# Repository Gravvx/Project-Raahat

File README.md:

# 🚁 Project RAAHAT
> **Rapid Aerial AI for Hazard Assessment & Tracking**  
> *Developed by Team Sutra for the Smart India Hackathon*

Project RAAHAT is an Edge-AI powered autonomous UAV reconnaissance system designed for rapid disaster search-and-rescue (SAR) operations. 

Built for the Smart India Hackathon, the platform utilizes a **Software-in-the-Loop (SITL)** architecture to simulate drone flight physics, perform entirely offline on-device AI inference, and mathematically map 2D video pixel detections into precise 3D real-world GPS coordinates for emergency responders — backed by a validated custom hardware payload designed for real-world deployment.

---

## 📑 Table of Contents
- [System Architecture](#-system-architecture)
- [Hardware Architecture](#-hardware-architecture)
- [Directory Structure](#-directory-structure)
- [Mathematical Core: Pixel-to-GPS](#-mathematical-core-pixel-to-gps)
- [Installation & Prerequisites](#-installation--prerequisites)
- [Operational Guide (Usage)](#-operational-guide-usage)
- [Dashboard Features (ARES-C2)](#-dashboard-features-ares-c2)

---

## 🏗️ System Architecture

To ensure safety, rapid iteration, and hardware-readiness, Project RAAHAT is built on **4 foundational pillars**:

1. **SITL Simulation (Webots):** Simulates a DJI Mavic 2 Pro with physically accurate IMU, GPS, and optical sensors. The Python-based controller acts as the flight computer, running Boustrophedon (lawnmower) autonomous search patterns via PID stabilization.
2. **Edge-AI Computer Vision:** Utilizes YOLOv8n optimized for edge GPUs alongside ByteTrack. This ensures real-time victim detection while preventing duplicate counting of the same survivor across consecutive video frames.
3. **Hardware Payload & Power System:** A custom-designed carrier PCB integrating the compute, sensing, and communication stack onto the physical airframe.
4. **ARES-C2 Ground Control Station:** A monolithic, Python-native Streamlit dashboard styled to MIL-STD-1472H defense ergonomics. It provides responders with live telemetry, offline map rendering, and geo-triage audit logs.

---

## 🔧 Hardware Architecture

Project RAAHAT's hardware stack is engineered so all AI inference happens onboard, ensuring functionality even when network connectivity is entirely unavailable at a disaster site.

### Compute & Sensing

| Component | Role |
| :--- | :--- |
| **NVIDIA Jetson Orin Nano** | Edge AI compute — runs YOLOv8n inference locally (CUDA-accelerated) |
| **RGB Camera** | Visual-spectrum survivor and hazard detection |
| **Thermal Camera (LWIR)** | Heat-signature detection for survivors under debris / low-visibility conditions |
| **Pixhawk / STM32** | Real-time flight stabilization, independent of the AI compute layer |
| **NEO-M8N GPS Module** | Positioning data for geo-tagging detections |
| **IMU + Barometer** | Orientation and altitude sensing, feeds flight controller |
| **SX1276 LoRa Transceiver** | Long-range, low-bandwidth telemetry link to ground station (868 MHz) |

### Power System

| Component | Spec |
| :--- | :--- |
| **Main Battery** | 4S / 6S LiPo |
| **Buck Converter (Compute Rail)** | 19V / 5A → Jetson Orin Nano |
| **Buck Converter (Avionics Rail)** | 5V / 4A → Flight controller, IMU, GPS |
| **Power Distribution Board (PDB)** | Routes raw battery voltage to ESCs/motors and both converted rails |

### Custom Carrier PCB & Physical Integration
* **KiCad Verification:** Fully designed project schematic verified with zero Electrical Rules Check (ERC) errors.
* **RF Optimization:** Includes a Pi-filter LC matching network for optimal LoRa RF output on 868 MHz.
* **Physical Assembly:** Sourced accurate `.STEP` CAD files for the airframe, Jetson Orin Nano, and FPV camera module to verify 30.5 × 30.5 mm standoff mounting feasibility and dual payload bay clearance.

### Data Flow (Hardware → Software Bridge)

```text
[RGB + Thermal Cameras] ──▶ Jetson Orin Nano (YOLOv8 Inference)
                                      │
[Pixhawk GPS/IMU] ─────────▶ MAVLink  │
                             Telemetry│
                                      ▼
                        [Compact JSON Alert] 
                                      │
                                    (UART)
                                      │
                                      ▼
                          [LoRa Transmitter (SX1276)]
                                      │
                                (868 MHz RF)
                                      │
                                      ▼
                          [Ground Base Station]
                                      │
                                      ▼
                             [ARES-C2 Dashboard]

SIH_DRONE_PROJECT/
├── webots/                     # SITL Simulation Environment
│   ├── controllers/
│   │   └── autonomous_patrol/
│   │       ├── autonomous_patrol.py  # Drone Flight Controller & PID Logic
│   │       ├── telemetry.json        # Live data bridge to GCS
│   │       └── yolov8n.pt            # Edge AI Model weights
│   ├── mavic2pro/              # UAV Physical Models & Protocols
│   └── worlds/                 # Simulated Disaster Environments
├── hardware/                   # Physical Hardware Design Assets
│   ├── pcb/
│   │   ├── DRONE_SIH.kicad_sch  # Schematic
│   │   └── DRONE_SIH.kicad_pcb  # Board layout (Edge.Cuts verified)
│   ├── cad/
│   │   ├── airframe.step             # Drone airframe STEP file
│   │   ├── jetson_orin_nano.step     # Compute module STEP file
│   │   └── fpv_camera.step           # Camera module STEP file
│   └── renders/                      # KiCad 3D raytraced board renders
├── dashboard.py                # ARES-C2 Tactical Ground Control UI
├── test_ai.py                  # Standalone YOLO inference testing script
└── yolov8n.pt                  # Root AI weights for local dashboard video testing

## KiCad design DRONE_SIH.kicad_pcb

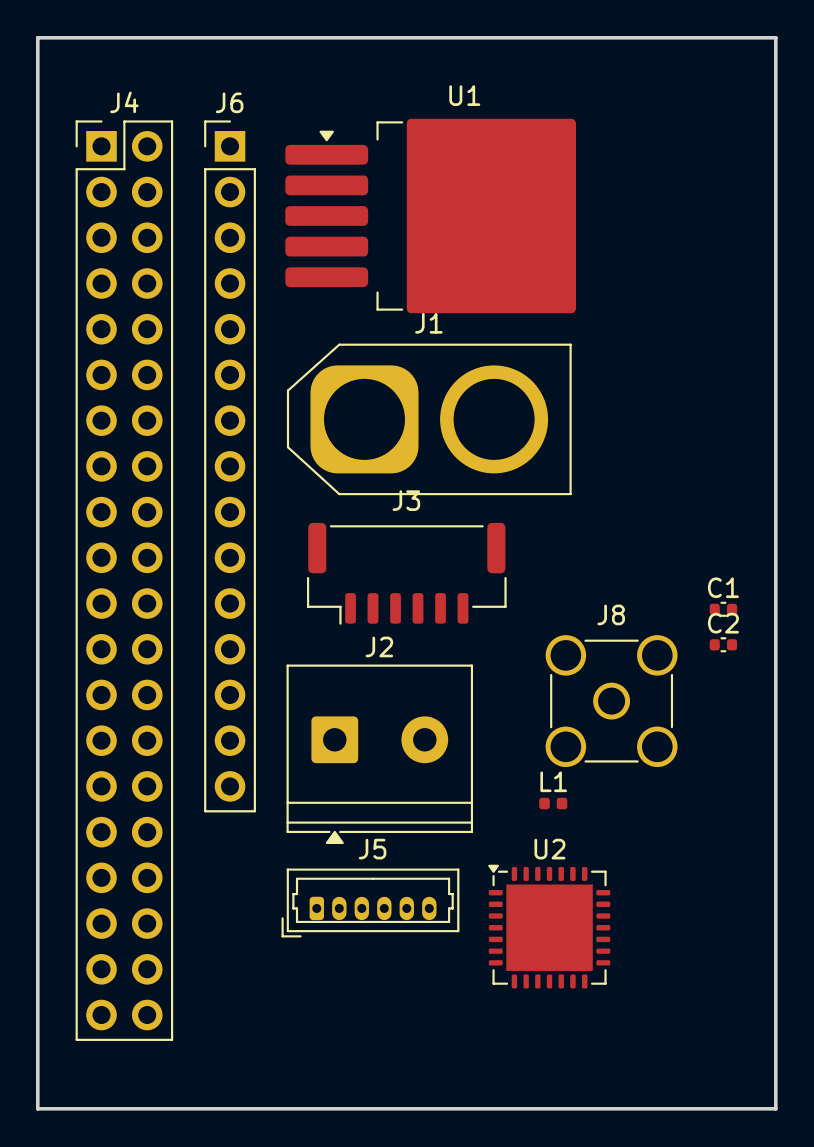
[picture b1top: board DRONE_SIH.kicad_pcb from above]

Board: 2 copper layers, 41.0 x 59.5 mm, 12 parts (0 on the bottom side), 13 nets, no tracks yet.

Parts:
C1: 3.3pF; C_0402_1005Metric
C2: 3.3pH; C_0402_1005Metric
J1: XT60-M; AMASS_XT60-M_1x02_P7.20mm_Vertical
J2: Conn_01x02; TerminalBlock_Phoenix_PT-1,5-2-5.0-H_1x02_P5.00mm_Horizontal
J3: Conn_01x06_Pin; JST_GH_BM06B-GHS-TBT_1x06-1MP_P1.25mm_Vertical
J4: Raspberry_Pi_2_3; PinHeader_2x20_P2.54mm_Vertical
J5: Conn_01x06_Pin; Molex_PicoBlade_53047-0610_1x06_P1.25mm_Vertical
J6: Conn_01x15_Pin; PinHeader_1x15_P2.54mm_Vertical
J8: Conn_Coaxial; SMA_Amphenol_132134-11_Vertical
L1: 4.7nH; L_0402_1005Metric
U1: LM2596S-5; TO-263-5_TabPin3
U2: SX1276; QFN-28-1EP_6x6mm_P0.65mm_EP4.8x4.8mm

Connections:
unnamed: C1.2, C2.2, L1.1
unnamed: J2.2, J4.6 (GND), J4.9 (GND), J4.14 (GND), J4.20 (GND), J4.25 (GND), J4.30 (GND), J4.34 (GND), J4.39 (GND), L1.2, U1.3 (GND), U1.5 (~ON/OFF), U2.15 (GND), U2.23 (GND), U2.26 (GND), U2.29 (GND)
unnamed: U1.2 (OUT), U1.4 (FB)
unnamed: J4.22 (GPIO25), U2.8 (DIO0)
unnamed: J4.21 (MISO0/GPIO9), U2.17 (MISO)
unnamed: J4.19 (MOSI0/GPIO10), U2.18 (MOSI)
unnamed: J4.23 (SCLK0/GPIO11), U2.16 (SCK)
unnamed: J4.24 (~CE0/GPIO8), U2.19 (NSS)
unnamed: J4.1 (3V3), J4.17 (3V3)
unnamed: C2.1, J8.2 (Ext)
unnamed: J8.1 (In), U2.27 (PA_BOOST)
unnamed: C1.1, U2.1 (RFI_LF)
unnamed: J4.2 (5V), J4.4 (5V), U2.3 (VBAT_ANA)

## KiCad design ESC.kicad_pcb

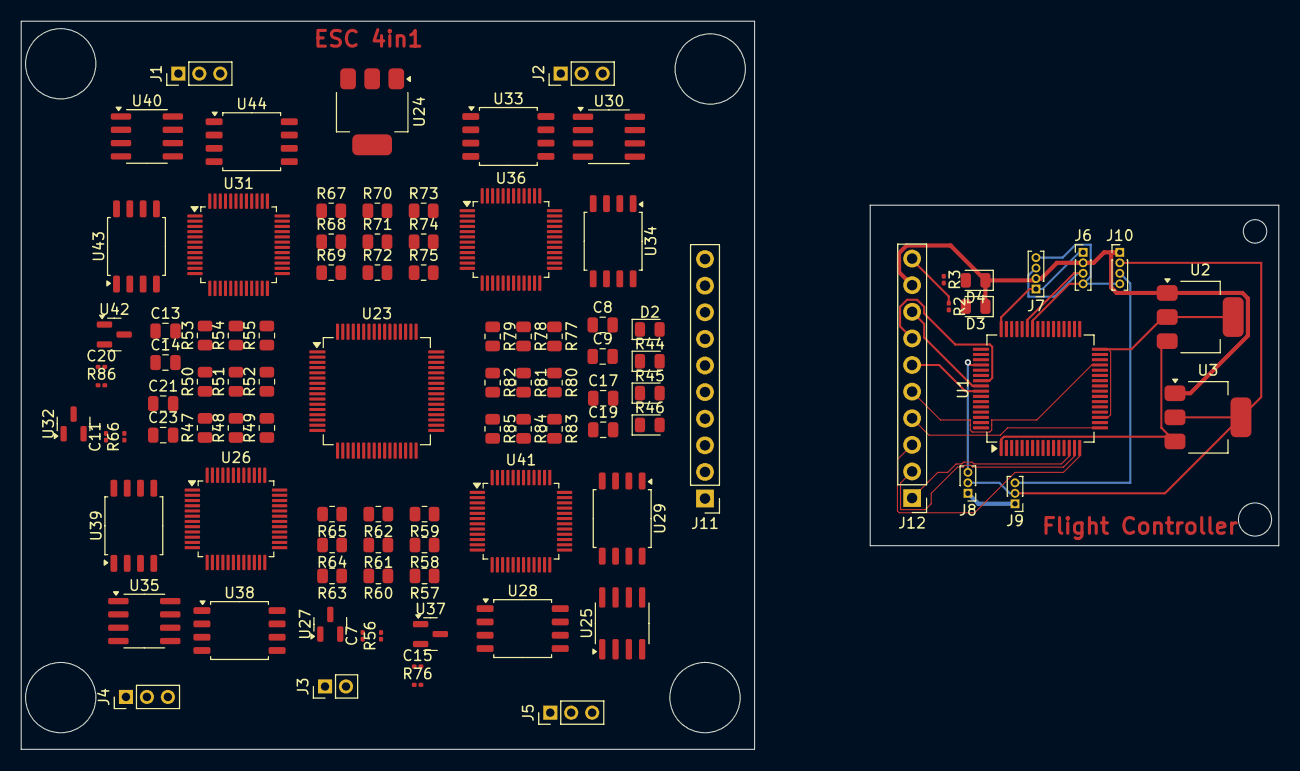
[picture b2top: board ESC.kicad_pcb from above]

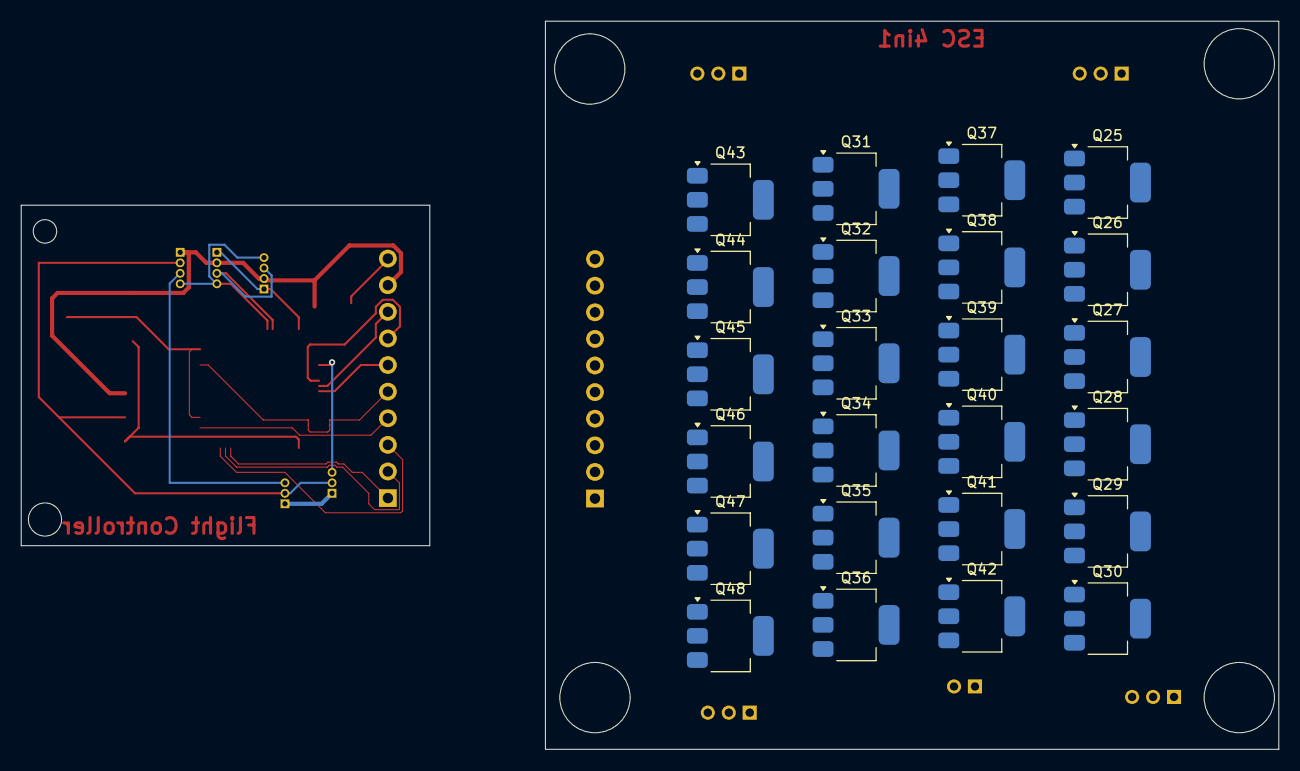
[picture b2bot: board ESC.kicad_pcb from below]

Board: 4 copper layers, 70.0 x 69.5 mm, 121 parts (24 on the bottom side), 148 nets.

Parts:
C7, C11, C15, C20: 100nF; C_0201_0603Metric
C8, C13, C17, C21: 1uF; C_0805_2012Metric
C9, C14, C19, C23: 10uF; C_0805_2012Metric
D2: LED; LED_0805_2012Metric
D3: ESC_status; LED_0805_2012Metric
D4: OC_STATUS; LED_0805_2012Metric
J1, J2, J4, J5: Conn_01x03_Pin; PinHeader_1x03_P2.00mm_Vertical
J3: Conn_01x02_Pin; PinHeader_1x02_P2.00mm_Vertical
J6: UART connector; PinHeader_1x04_P1.00mm_Vertical
J7: GPS NEO6M; PinHeader_1x04_P1.00mm_Vertical
J8: RC_erciever; PinHeader_1x03_P1.00mm_Vertical
J9: FVP_CAMERA; PinHeader_1x03_P1.00mm_Vertical
J10: VTx; PinHeader_1x04_P1.00mm_Vertical
J11: ESC_PIN; PinHeader_1x10_P2.54mm_Vertical
J12: FC_PIN; PinHeader_1x10_P2.54mm_Vertical
Q25, Q26, Q27, Q28, Q29, Q30, Q31, Q32, Q33, Q34, Q35, Q36, Q37, Q38, Q39, Q40, Q41, Q42, Q43, Q44, Q45, Q46, Q47, Q48: NMOS; SOT-223-3_TabPin2
R2, R3: 330Ω; R_0201_0603Metric
R44: 1kΩ; LED_0805_2012Metric
R45, R46: 10kΩ; LED_0805_2012Metric
R47, R48, R49, R57, R58, R59, R67, R68, R69, R77, R78, R79: 10kΩ; R_0805_2012Metric
R50, R51, R52, R53, R54, R55, R60, R61, R62, R63, R64, R65, R70, R71, R72, R73, R74, R75, R80, R81, R82, R83, R84, R85: 10Ω; R_0805_2012Metric
R56, R66, R76, R86: 0.01Ω; R_0201_0603Metric
U1, U23: STM32F405RGTx; LQFP-64_10x10mm_P0.5mm
U2, U24: AMS1117-3.3; SOT-223-3_TabPin2
U3: AMS1117CD-5.0; SOT-223-3_TabPin2
U25, U30, U35, U40: LM35-D; SOIC-8_3.9x4.9mm_P1.27mm
U26, U31, U36, U41: DRV8323RHRGZT; TQFP-48_7x7mm_P0.5mm
U27, U32, U37, U42: LM4040DBZ-2.0; SOT-23
U28, U33, U38, U43: LM358; SOIC-8_5.3x5.3mm_P1.27mm
U29, U34, U39, U44: LM393; SOIC-8_5.3x5.3mm_P1.27mm

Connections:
+BATT: U1.1 (VBAT), U2.3 (VI), U3.3 (VI)
/ESC_4in1/DSHOT_1: J11.1, U23.34 (PB13)
/ESC_4in1/DSHOT_2: J11.2, U23.35 (PB14)
/ESC_4in1/DSHOT_3: J11.3, U23.36 (PB15)
/ESC_4in1/DSHOT_4: J11.4, U23.44 (PA11)
/ESC_4in1/ESC_motor1/3.3V: R46.1, R47.1, R48.1, R49.1, R57.1, R58.1, R59.1, R67.1, R68.1, R69.1, R77.1, R78.1, R79.1, U23.13 (VDDA), U23.19 (VDD), U23.32 (VDD), U23.48 (VDD), U23.64 (VDD), U24.2 (VO), U25.8 (+V_{S}), U26.16 (DVDD), U30.8 (+V_{S}), U31.16 (DVDD), U35.8 (+V_{S}), U36.16 (DVDD), U40.8 (+V_{S}), U41.16 (DVDD)
/ESC_4in1/ESC_motor1/+BATT: C9.1, C14.1, C19.1, C23.1, J3.2, Q25.1 (D), Q27.1 (D), Q29.1 (D), Q31.1 (D), Q33.1 (D), Q35.1 (D), Q37.1 (D), Q39.1 (D), Q41.1 (D), Q43.1 (D), Q45.1 (D), Q47.1 (D), U23.1 (VBAT), U24.3 (VI), U26.6 (VM), U31.6 (VM), U36.6 (VM), U41.6 (VM)
/ESC_4in1/ESC_motor1/I_SENSE_M: U23.11 (PC3), U37.1 (K), U38.1, U39.3 (+)
/ESC_4in1/ESC_motor1/PHASE_A: J5.1, Q37.3 (S), Q38.1 (D)
/ESC_4in1/ESC_motor1/PHASE_B: J5.2, Q39.3 (S), Q40.1 (D)
/ESC_4in1/ESC_motor1/PHASE_C: J5.3, Q41.3 (S), Q42.1 (D)
/ESC_4in1/ESC_motor1/PWM_B: U23.42 (PA9), U36.39 (INHB)
/ESC_4in1/ESC_motor1/PWM_C: U23.43 (PA10), U36.41 (INHC)
/ESC_4in1/ESC_motor1/SCLK: U23.21 (PA5), U26.36 (SCLK), U31.36 (SCLK), U36.36 (SCLK), U41.36 (SCLK)
/ESC_4in1/ESC_motor1/SDI: U23.23 (PA7), U26.35 (SDI), U31.35 (SDI), U36.35 (SDI), U41.35 (SDI)
/ESC_4in1/ESC_motor1/SDO: U23.22 (PA6), U26.33 (13), U31.33 (13), U36.33 (13), U41.33 (13)
/ESC_4in1/ESC_motor1/TEMP_M: U23.17 (PA3), U35.1 (V_{OUT})
/ESC_4in1/ESC_motor1/nSCS: U23.20 (PA4), U36.34 (nSCS)
/ESC_4in1/ESC_motor2/I_SENSE_M: U23.10 (PC2), U42.1 (K), U43.1, U44.3 (+)
/ESC_4in1/ESC_motor2/OC_prot: U23.24 (PC4), U44.1
/ESC_4in1/ESC_motor2/PHASE_A: J4.1, Q43.3 (S), Q44.1 (D)
/ESC_4in1/ESC_motor2/PHASE_B: J4.2, Q45.3 (S), Q46.1 (D)
/ESC_4in1/ESC_motor2/PHASE_C: J4.3, Q47.3 (S), Q48.1 (D)
/ESC_4in1/ESC_motor2/PWM_A: U23.14 (PA0), U41.37 (INHA)
/ESC_4in1/ESC_motor2/PWM_B: U23.15 (PA1), U41.39 (INHB)
/ESC_4in1/ESC_motor2/PWM_C: U23.16 (PA2), U41.41 (INHC)
/ESC_4in1/ESC_motor2/TEMP_M: U23.27 (PB1), U40.1 (V_{OUT})
/ESC_4in1/ESC_motor2/nSCS: U23.29 (PB10), U41.34 (nSCS)
/ESC_4in1/ESC_motor3/I_SENSE_M: U23.8 (PC0), U32.1 (K), U33.1, U34.3 (+)
/ESC_4in1/ESC_motor3/OC_prot: U23.55 (PB3), U34.1
/ESC_4in1/ESC_motor3/PHASE_A: J2.1, Q31.3 (S), Q32.1 (D)
/ESC_4in1/ESC_motor3/PHASE_B: J2.2, Q33.3 (S), Q34.1 (D)
/ESC_4in1/ESC_motor3/PHASE_C: J2.3, Q35.3 (S), Q36.1 (D)
/ESC_4in1/ESC_motor3/PWM_A: U23.37 (PC6), U31.37 (INHA)
/ESC_4in1/ESC_motor3/PWM_B: U23.38 (PC7), U31.39 (INHB)
/ESC_4in1/ESC_motor3/PWM_C: U23.39 (PC8), U31.41 (INHC)
/ESC_4in1/ESC_motor3/TEMP_M: U23.26 (PB0), U30.1 (V_{OUT})
/ESC_4in1/ESC_motor3/nSCS: U23.33 (PB12), U31.34 (nSCS)
/ESC_4in1/ESC_motor4/I_SENSE_M: U23.9 (PC1), U27.1 (K), U28.1, U29.3 (+)
/ESC_4in1/ESC_motor4/OC_prot: U23.50 (PA15), U29.1
/ESC_4in1/ESC_motor4/PHASE_A: J1.1, Q25.3 (S), Q26.1 (D)
/ESC_4in1/ESC_motor4/PHASE_B: J1.2, Q27.3 (S), Q28.1 (D)
/ESC_4in1/ESC_motor4/PHASE_C: J1.3, Q29.3 (S), Q30.1 (D)
/ESC_4in1/ESC_motor4/PWM_A: U23.58 (PB6), U26.37 (INHA)
/ESC_4in1/ESC_motor4/PWM_B: U23.59 (PB7), U26.39 (INHB)
/ESC_4in1/ESC_motor4/PWM_C: U23.61 (PB8), U26.41 (INHC)
/ESC_4in1/ESC_motor4/TEMP_M: U23.25 (PC5), U25.1 (V_{OUT})
/ESC_4in1/ESC_motor4/nSCS: U23.30 (PB11), U26.34 (nSCS)
/ESC_4in1/LED_STATUS: J11.10, U23.41 (PA8), U36.37 (INHA)
/ESC_4in1/OC_STATUS: U23.57 (PB5), U39.1
/ESC_4in1/SCLK2: J11.6, U23.51 (PC10)
/ESC_4in1/SDI2: J11.7, U23.53 (PC12)
/ESC_4in1/SDO2: J11.8, U23.52 (PC11)
/ESC_4in1/nSCS2: J11.5, U23.28 (PB2)
GND: C8.2, C9.2, C13.2, C14.2, C17.2, C19.2, C21.2, C23.2, D2.1 (K), D3.1 (K), D4.1 (K), J3.1, J6.2, J7.2, J8.1, J9.1, J10.1, J11.9, J12.9, R45.2, U1.12 (VSSA), U1.18 (VSS), U1.63 (VSS), U2.1 (GND), U3.1 (GND), U23.12 (VSSA), U23.18 (VSS), U23.63 (VSS), U24.1 (GND), U25.4 (GND), U26.2 (PGND), U26.12 (AGND), U26.27 (DGND), U26.43 (BGND), U30.4 (GND), U31.2 (PGND), U31.12 (AGND), U31.27 (DGND), U31.43 (BGND), U35.4 (GND), U36.2 (PGND), U36.12 (AGND), U36.27 (DGND), U36.43 (BGND), U40.4 (GND), U41.2 (PGND), U41.12 (AGND), U41.27 (DGND), U41.43 (BGND)
unnamed: D2.2 (A), R44.1
unnamed: D3.2 (A), R2.2
unnamed: D4.2 (A), R3.2
unnamed: J6.1, J7.1, U1.13 (VDDA), U1.19 (VDD), U1.32 (VDD), U1.48 (VDD), U1.64 (VDD), U2.2 (VO)
unnamed: J6.3, J7.3, U1.43 (PA10)
unnamed: J8.3, U1.52 (PC11)
unnamed: J8.2, J9.2, J10.2, U3.2 (VO)
unnamed: J9.3, J10.3
unnamed: J6.4, J7.4, J10.4, U1.42 (PA9)
unnamed: J12.1, U1.14 (PA0)
unnamed: J12.2, U1.15 (PA1)
unnamed: J12.3, U1.16 (PA2)
unnamed: J12.4, U1.17 (PA3)
unnamed: J12.5, U1.29 (PB10)
unnamed: J12.6, U1.57 (PB5)
unnamed: J12.7, U1.55 (PB3)
unnamed: J12.8, U1.56 (PB4)
unnamed: J12.10, R2.1
unnamed: Q25.2 (G), R51.2
unnamed: Q26.2 (G), R52.2
unnamed: Q26.3 (S), Q28.3 (S), Q30.3 (S), R56.1 (S)
unnamed: Q27.2 (G), R53.2
unnamed: Q28.2 (G), R54.2
unnamed: Q29.2 (G), R55.2
unnamed: Q30.2 (G), R50.2
unnamed: Q31.2 (G), R61.2
unnamed: Q32.2 (G), R62.2
unnamed: Q32.3 (S), Q34.3 (S), Q36.3 (S), R66.1 (S)
unnamed: Q33.2 (G), R63.2
unnamed: Q34.2 (G), R64.2
unnamed: Q35.2 (G), R65.2
unnamed: Q36.2 (G), R60.2
unnamed: Q37.2 (G), R71.2
unnamed: Q38.2 (G), R72.2
unnamed: Q38.3 (S), Q40.3 (S), Q42.3 (S), R76.1 (S)
unnamed: Q39.2 (G), R73.2
unnamed: Q40.2 (G), R74.2
unnamed: Q41.2 (G), R75.2
unnamed: Q42.2 (G), R70.2
unnamed: Q43.2 (G), R81.2
unnamed: Q44.2 (G), R82.2
unnamed: Q44.3 (S), Q46.3 (S), Q48.3 (S), R86.1 (S)
unnamed: Q45.2 (G), R83.2
unnamed: Q46.2 (G), R84.2
unnamed: Q47.2 (G), R85.2
unnamed: Q48.2 (G), R80.2
unnamed: R45.1, U23.60 (BOOT0)
unnamed: R46.2, U23.7 (NRST)
unnamed: R44.2, U23.40 (PC9)
unnamed: C7.1, U26.4 (CPH)
unnamed: R51.1, U26.8 (GHA)
unnamed: R53.1, U26.17 (GHB)
unnamed: R55.1, U26.18 (GHC)
unnamed: R52.1, U26.10 (GLA)
unnamed: R54.1, U26.15 (GLB)
unnamed: R50.1, U26.20 (GLC)
unnamed: R49.2, U26.28 (NFAULT)
unnamed: C7.2, C8.1, U26.5 (VCP)
unnamed: R47.2, U27.2 (A), U29.2 (-)
unnamed: R56.2, U28.2 (-)
unnamed: C11.1, U31.4 (CPH)
unnamed: R61.1, U31.8 (GHA)
unnamed: R63.1, U31.17 (GHB)
unnamed: R65.1, U31.18 (GHC)
unnamed: R62.1, U31.10 (GLA)
unnamed: R64.1, U31.15 (GLB)
unnamed: R60.1, U31.20 (GLC)
unnamed: R59.2, U31.28 (NFAULT)
unnamed: C11.2, C13.1, U31.5 (VCP)
unnamed: R57.2, U32.2 (A), U34.2 (-)
unnamed: R66.2, U33.2 (-)
unnamed: C15.1, U36.4 (CPH)
unnamed: R71.1, U36.8 (GHA)
unnamed: R73.1, U36.17 (GHB)
unnamed: R75.1, U36.18 (GHC)
unnamed: R72.1, U36.10 (GLA)
unnamed: R74.1, U36.15 (GLB)
unnamed: R70.1, U36.20 (GLC)
unnamed: R69.2, U36.28 (NFAULT)
unnamed: C15.2, C17.1, U36.5 (VCP)
unnamed: R67.2, U37.2 (A), U39.2 (-)
unnamed: R76.2, U38.2 (-)
unnamed: C20.1, U41.4 (CPH)
unnamed: R81.1, U41.8 (GHA)
unnamed: R83.1, U41.17 (GHB)
unnamed: R85.1, U41.18 (GHC)
unnamed: R82.1, U41.10 (GLA)
unnamed: R84.1, U41.15 (GLB)
unnamed: R80.1, U41.20 (GLC)
unnamed: R79.2, U41.28 (NFAULT)
unnamed: C20.2, C21.1, U41.5 (VCP)
unnamed: R77.2, U42.2 (A), U44.2 (-)
unnamed: R86.2, U43.2 (-)
